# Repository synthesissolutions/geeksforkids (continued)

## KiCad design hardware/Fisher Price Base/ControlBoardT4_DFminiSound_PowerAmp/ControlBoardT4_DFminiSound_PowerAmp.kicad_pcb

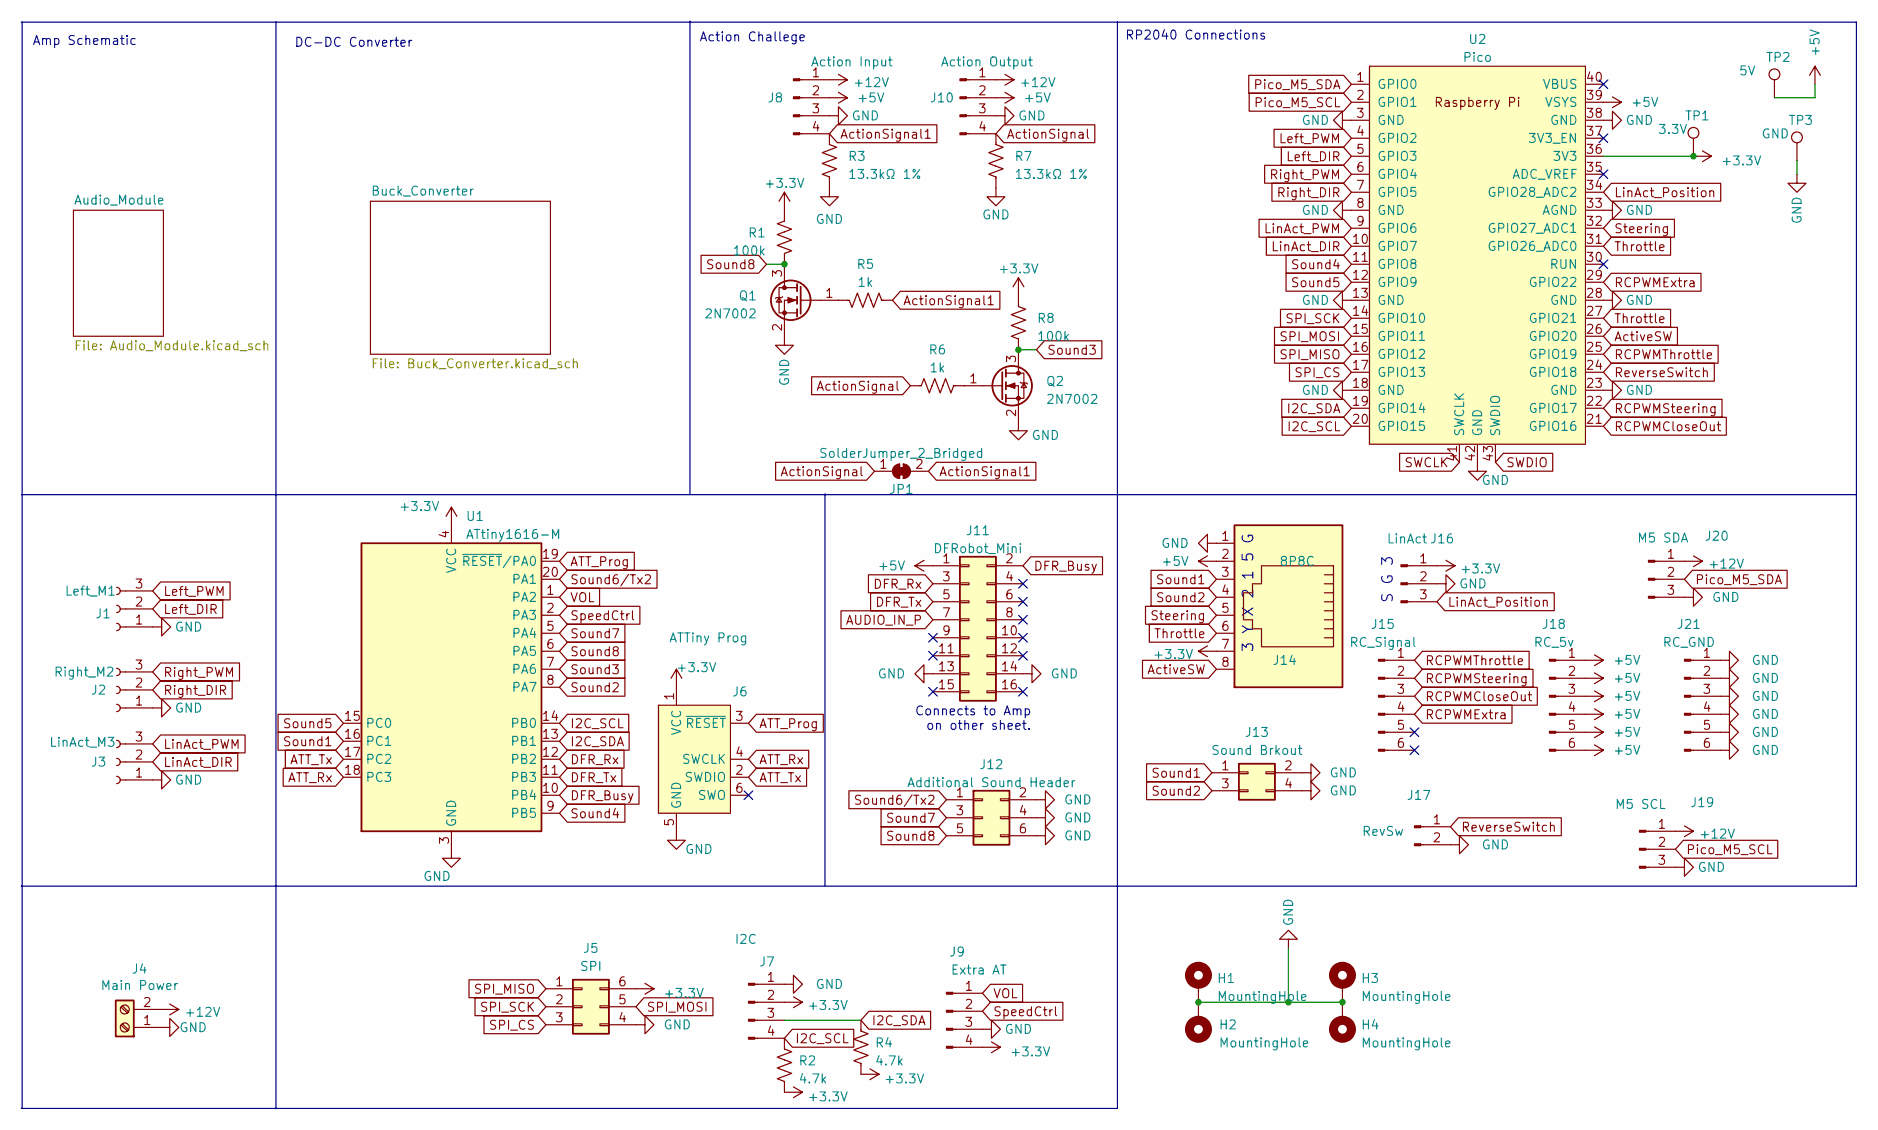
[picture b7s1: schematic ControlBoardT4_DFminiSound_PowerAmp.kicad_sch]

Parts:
H1, H2, H3, H4: MountingHole; MountingHole_2.7mm_M2.5_Pad
J1: Left_M1; PinHeader_1x03_P2.54mm_Vertical
J2: Right_M2; PinHeader_1x03_P2.54mm_Vertical
J3: LinAct_M3; PinHeader_1x03_P2.54mm_Vertical
J4: Main Power; TerminalBlock_bornier-2_P5.08mm
J5: SPI; PinHeader_2x03_P2.54mm_Vertical
J6: ATTiny Prog; Tag-Connect_TC2030-IDC-NL_2x03_P1.27mm_Vertical
J7: I2C; PinHeader_1x04_P2.54mm_Vertical
J8: Action Input; JST_XH_B4B-XH-A_1x04_P2.50mm_Vertical
J9: Extra AT; PinHeader_1x04_P2.54mm_Vertical
J10: Action Output; JST_XH_B4B-XH-A_1x04_P2.50mm_Vertical
J11: DFRobot_Mini; DFRobotMini_2x08_P2.54mm_Vertical
J12: Additional Sound Header; PinSocket_2x03_P2.54mm_Vertical
J13: Sound Brkout; PinSocket_2x02_P2.54mm_Vertical
J14: 8P8C; RJ45_x08_Tab_Up
J15: RC_Signal; PinSocket_1x06_P2.54mm_Vertical
J16: LinAct; JST_XH_B3B-XH-A_1x03_P2.54mm_Vertical
J17: RevSw; JST_XH_B2B-XH-A_1x02_P2.50mm_Vertical
J18: RC_5v; PinSocket_1x06_P2.54mm_Vertical
J19: M5 SCL; JST_XH_B3B-XH-A_1x03_P2.54mm_Vertical
J20: M5 SDA; JST_XH_B3B-XH-A_1x03_P2.54mm_Vertical
J21: RC_GND; PinSocket_1x06_P2.54mm_Vertical
JP1: SolderJumper_2_Bridged; SolderJumper-2_P1.3mm_Bridged_RoundedPad1.0x1.5mm
Q1, Q2: 2N7002; SOT-23; MPN C8545
R1, R8: 100k; R_0402_1005Metric; MPN C60491
R2, R4: 4.7k; R_0402_1005Metric; MPN C25900
R3, R7: 13.3kΩ 1%; R_0603_1608Metric; MPN C25952
R5, R6: 1k; R_0402_1005Metric; MPN C11702
TP1: 3.3V; TestPoint_Pad_1.5x1.5mm
TP2: 5V; TestPoint_Pad_1.5x1.5mm
TP3: GND; TestPoint_Pad_1.5x1.5mm
U1: ATtiny1616-M; VQFN-20-1EP_3x3mm_P0.4mm_EP1.7x1.7mm; MPN C507118
U2: Pico; RPi_Pico_SMD_TH

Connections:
+3.3V: J5.6, J6.1 (VCC), J7.2, J9.4, J14.7, J16.1, R1.1, R2.1, R4.1, R8.1, TP1.1, U1.4 (VCC), U2.36 (3V3)
+5V: J8.2, J10.2, J11.1, J14.2, J18.1, J18.2, J18.3, J18.4, J18.5, J18.6, TP2.1, U2.39 (VSYS); also elsewhere on the board
+12V: J4.2, J8.1, J10.1, J19.1, J20.1; also elsewhere on the board
ATT_Prog: J6.3 (~RESET), U1.19 (~RESET/PA0)
ATT_Rx: J6.4 (SWCLK), U1.18 (PC3)
ATT_Tx: J6.2 (SWDIO), U1.17 (PC2)
AUDIO_IN_P: J11.7; also elsewhere on the board
ActionSignal: J10.4, JP1.1 (A), R6.1, R7.1
ActionSignal1: J8.4, JP1.2 (B), R3.1, R5.1
ActiveSW: J14.8, U2.26 (GPIO20)
DFR_Busy: J11.2, U1.10 (PB4)
DFR_Rx: J11.3, U1.12 (PB2)
DFR_Tx: J11.5, U1.11 (PB3)
GND: H1.1, H2.1, H3.1, H4.1, J1.1, J2.1, J3.1, J4.1, J5.4, J6.5 (GND), J7.1, J8.3, J9.3, J10.3, J11.13, J11.14, J12.2, J12.4, J12.6, J13.2, J13.4, J14.1, J16.2, J17.2, J19.3, J20.3, J21.1, J21.2, J21.3, J21.4, J21.5, J21.6, Q1.2 (S), Q2.2 (S), R3.2, R7.2, TP3.1, U1.3 (GND), U1.21 (GND), U2.3 (GND), U2.8 (GND), U2.13 (GND), U2.18 (GND), U2.23 (GND), U2.28 (GND), U2.33 (AGND), U2.38 (GND), U2.42 (GND); also elsewhere on the board
I2C_SCL: J7.4, R2.2, U1.14 (PB0), U2.20 (GPIO15)
I2C_SDA: J7.3, R4.2, U1.13 (PB1), U2.19 (GPIO14)
Left_DIR: J1.2, U2.5 (GPIO3)
Left_PWM: J1.3, U2.4 (GPIO2)
LinAct_DIR: J3.2, U2.10 (GPIO7)
LinAct_PWM: J3.3, U2.9 (GPIO6)
LinAct_Position: J16.3, U2.34 (GPIO28_ADC2)
unnamed: Q1.1 (G), R5.2
unnamed: Q2.1 (G), R6.2
Pico_M5_SCL: J19.2, U2.2 (GPIO1)
Pico_M5_SDA: J20.2, U2.1 (GPIO0)
RCPWMCloseOut: J15.3, U2.21 (GPIO16)
RCPWMExtra: J15.4, U2.29 (GPIO22)
RCPWMSteering: J15.2, U2.22 (GPIO17)
RCPWMThrottle: J15.1, U2.25 (GPIO19)
ReverseSwitch: J17.1, U2.24 (GPIO18)
Right_DIR: J2.2, U2.7 (GPIO5)
Right_PWM: J2.3, U2.6 (GPIO4)
SPI_CS: J5.3, U2.17 (GPIO13)
SPI_MISO: J5.1, U2.16 (GPIO12)
SPI_MOSI: J5.5, U2.15 (GPIO11)
SPI_SCK: J5.2, U2.14 (GPIO10)
SWCLK: U2.41 (SWCLK)
SWDIO: U2.43 (SWDIO)
Sound1: J13.1, J14.3, U1.16 (PC1)
Sound2: J13.3, J14.4, U1.8 (PA7)
Sound3: Q2.3 (D), R8.2, U1.7 (PA6)
Sound4: U1.9 (PB5), U2.11 (GPIO8)
Sound5: U1.15 (PC0), U2.12 (GPIO9)
Sound6/Tx2: J12.1, U1.20 (PA1)
Sound7: J12.3, U1.5 (PA4)
Sound8: J12.5, Q1.3 (D), R1.2, U1.6 (PA5)
SpeedCtrl: J9.2, U1.2 (PA3)
Steering: J14.5, U2.32 (GPIO27_ADC1)
Throttle: J14.6, U2.27 (GPIO21), U2.31 (GPIO26_ADC0)
VOL: J9.1, U1.1 (PA2)

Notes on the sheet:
Connects to Amp on other sheet.
3 Y X 2 1 5 G
RP2040 Connections
Amp Schematic
DC-DC Converter
Action Challege
S G 3

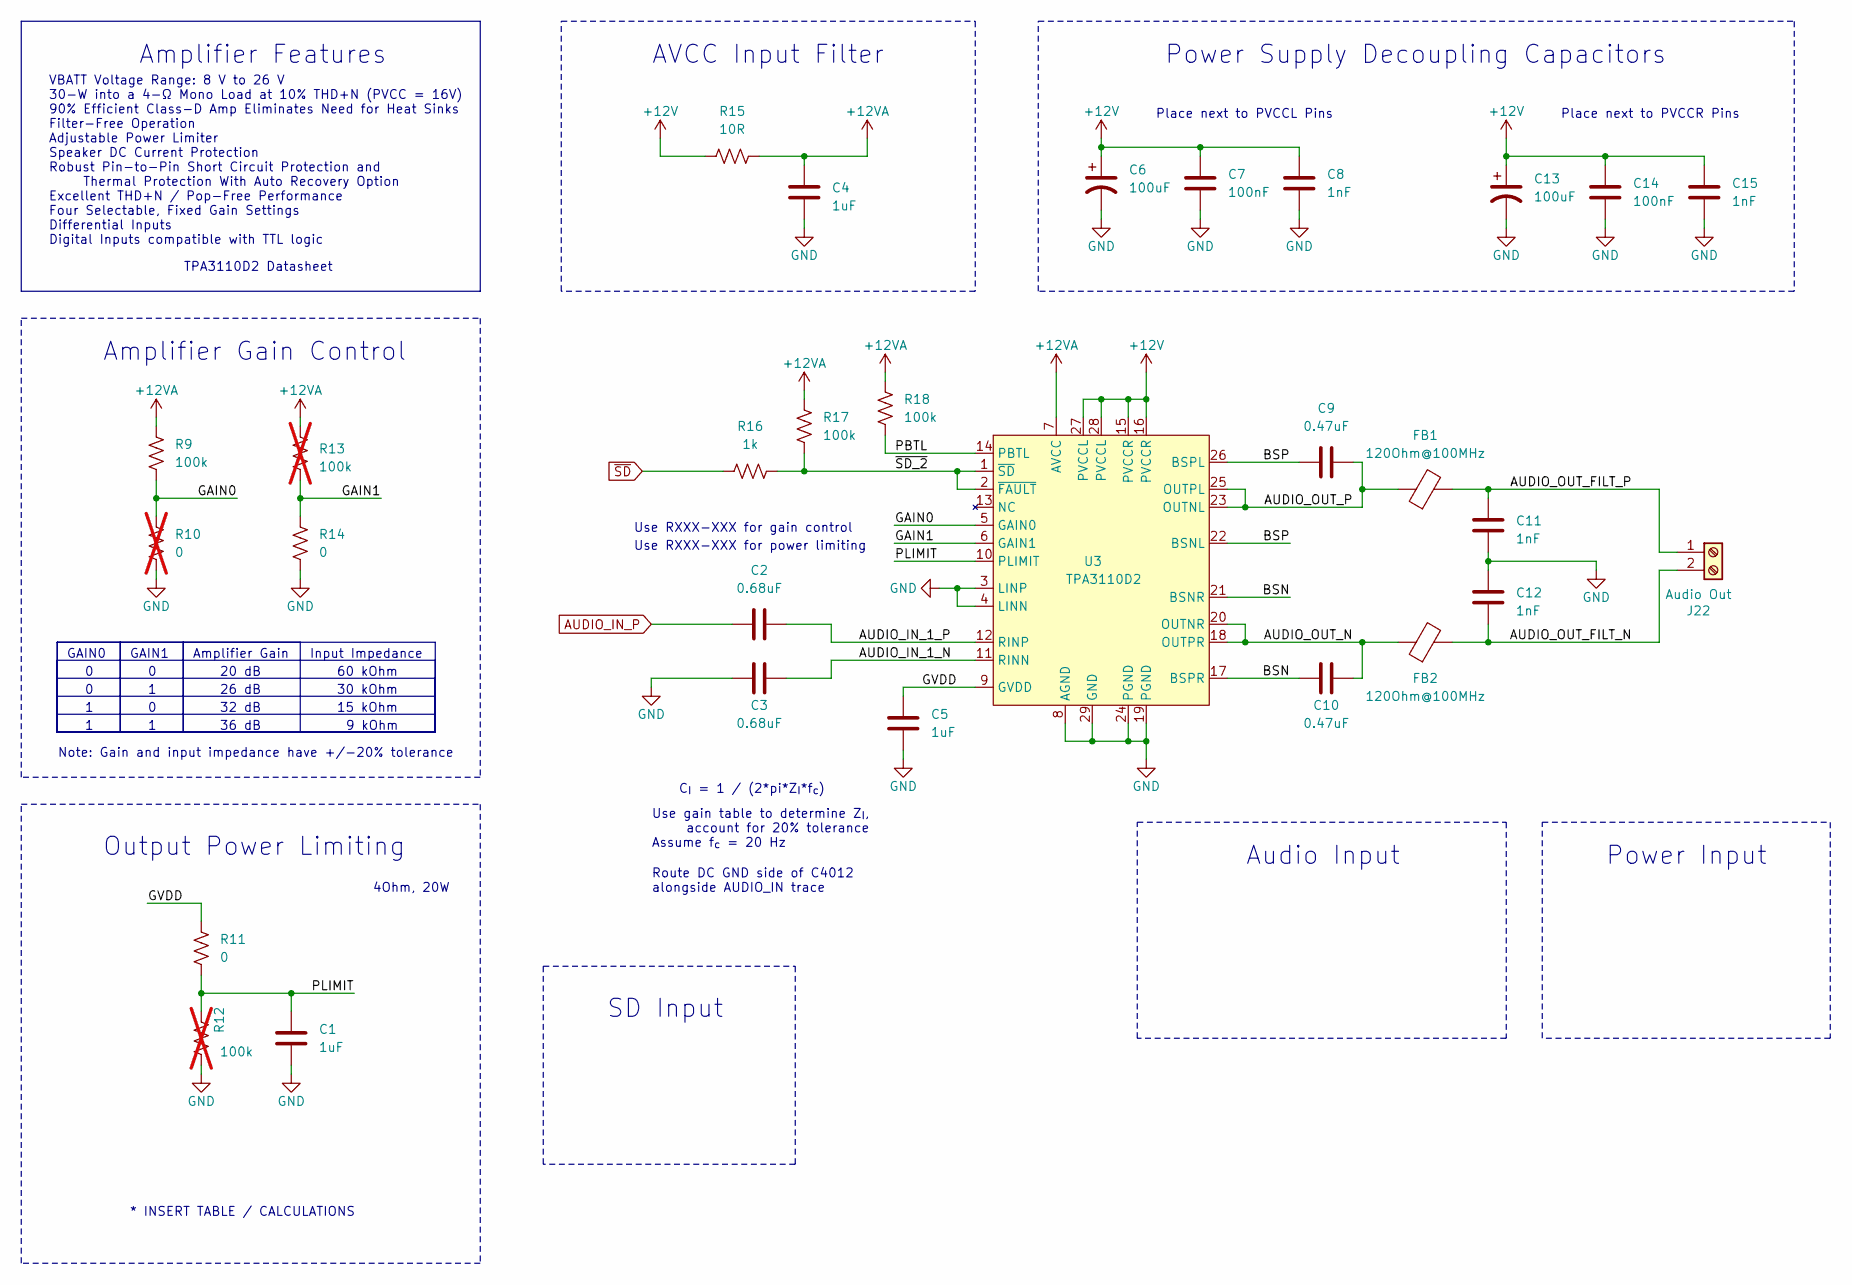
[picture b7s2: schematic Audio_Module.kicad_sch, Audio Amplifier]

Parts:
C1, C4, C5: 1uF; C_0402_1005Metric; MPN C1518208
C2, C3: 0.68uF; C_0402_1005Metric; MPN C113784
C6, C13: 100uF; CP_Radial_D8.0mm_P3.50mm; MPN C112510
C7, C14: 100nF; C_0402_1005Metric; MPN C105882
C8, C11, C12, C15: 1nF; C_0402_1005Metric; MPN C106205
C9, C10: 0.47uF; C_0402_1005Metric; MPN C437527
FB1, FB2: 120Ohm@100MHz; L_1206_3216Metric; MPN C3011219
J22: Audio Out; TerminalBlock_bornier-2_P5.08mm
R9, R17, R18: 100k; R_0402_1005Metric; MPN C60491
R10: 0; R_0402_1005Metric; MPN C17168; not fitted
R11, R14: 0; R_0402_1005Metric; MPN C17168
R12, R13: 100k; R_0402_1005Metric; MPN C60491; not fitted
R15: 10R; R_0603_1608Metric; MPN C22859
R16: 1k; R_0402_1005Metric; MPN C11702
U3: TPA3110D2; HTSSOP-28-1EP_4.4x9.7mm_P0.65mm_EP3.4x9.5mm_Mask2.4x6.17mm_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; MPN C30132

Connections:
+12V: C6.1, C7.1, C8.1, C13.1, C14.1, C15.1, R15.1, U3.15 (PVCCR), U3.16 (PVCCR), U3.27 (PVCCL), U3.28 (PVCCL); also elsewhere on the board
+12VA: C4.1, R9.1, R13.1, R15.2, R17.1, R18.1, U3.7 (AVCC)
/Audio_Module/AUDIO_IN_1_N: C3.1, U3.11 (RINN)
/Audio_Module/AUDIO_IN_1_P: C2.2, U3.12 (RINP)
/Audio_Module/AUDIO_OUT_FILT_N: C12.2, FB2.2, J22.2
/Audio_Module/AUDIO_OUT_FILT_P: C11.1, FB1.2, J22.1
/Audio_Module/AUDIO_OUT_N: C10.1, FB2.1, U3.18 (OUTPR), U3.20 (OUTNR)
/Audio_Module/AUDIO_OUT_P: C9.1, FB1.1, U3.23 (OUTNL), U3.25 (OUTPL)
/Audio_Module/BSN: C10.2, U3.17 (BSPR), U3.21 (BSNR)
/Audio_Module/BSP: C9.2, U3.22 (BSNL), U3.26 (BSPL)
/Audio_Module/GAIN0: R9.2, R10.1, U3.5 (GAIN0)
/Audio_Module/GAIN1: R13.2, R14.1, U3.6 (GAIN1)
/Audio_Module/GVDD: C5.1, R11.1, U3.9 (GVDD)
/Audio_Module/PBTL: R18.2, U3.14 (PBTL)
/Audio_Module/PLIMIT: C1.1, R11.2, R12.1, U3.10 (PLIMIT)
/Audio_Module/~SD_2: R16.2, R17.2, U3.1 (~SD), U3.2 (~FAULT)
AUDIO_IN_P: C2.1; also elsewhere on the board
GND: C1.2, C3.2, C4.2, C5.2, C6.2, C7.2, C8.2, C11.2, C12.1, C13.2, C14.2, C15.2, R10.2, R12.2, R14.2, U3.3 (LINP), U3.4 (LINN), U3.8 (AGND), U3.19 (PGND), U3.24 (PGND), U3.29 (GND); also elsewhere on the board
~SD: R16.1

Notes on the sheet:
30 kOhm
Route DC GND side of C4012 alongside AUDIO_IN trace
Use gain table to determine Z_{I}, account for 20% tolerance Assume f_{c} = 20 Hz
Use RXXX-XXX for power limiting
Amplifier Gain Control
GAIN0
Output Power Limiting
32 dB
C_{I} = 1 / (2*pi*Z_{I}*f_{c})
Use RXXX-XXX for gain control
20 dB
* INSERT TABLE / CALCULATIONS
SD Input
Audio Input
Note: Gain and input impedance have +/-20% tolerance
26 dB
VBATT Voltage Range: 8 V to 26 V 30-W into a 4-Ω Mono Load at 10% THD+N (PVCC = 16V) 90% Efficient Class-D Amp Eliminates Need for Heat Sinks Filter-Free Operation Adjustable Power Limiter Speaker DC Current Protection Robust Pin-to-Pin Short Circuit Protection and Thermal Protection With Auto Reco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
Amplifier Features
Amplifier Gain
Power Input
36 dB
4Ohm, 20W
TPA3110D2 Datasheet
AVCC Input Filter
15 kOhm
9 kOhm
Place next to PVCCR Pins
GAIN1
60 kOhm
Input Impedance
Power Supply Decoupling Capacitors
Place next to PVCCL Pins

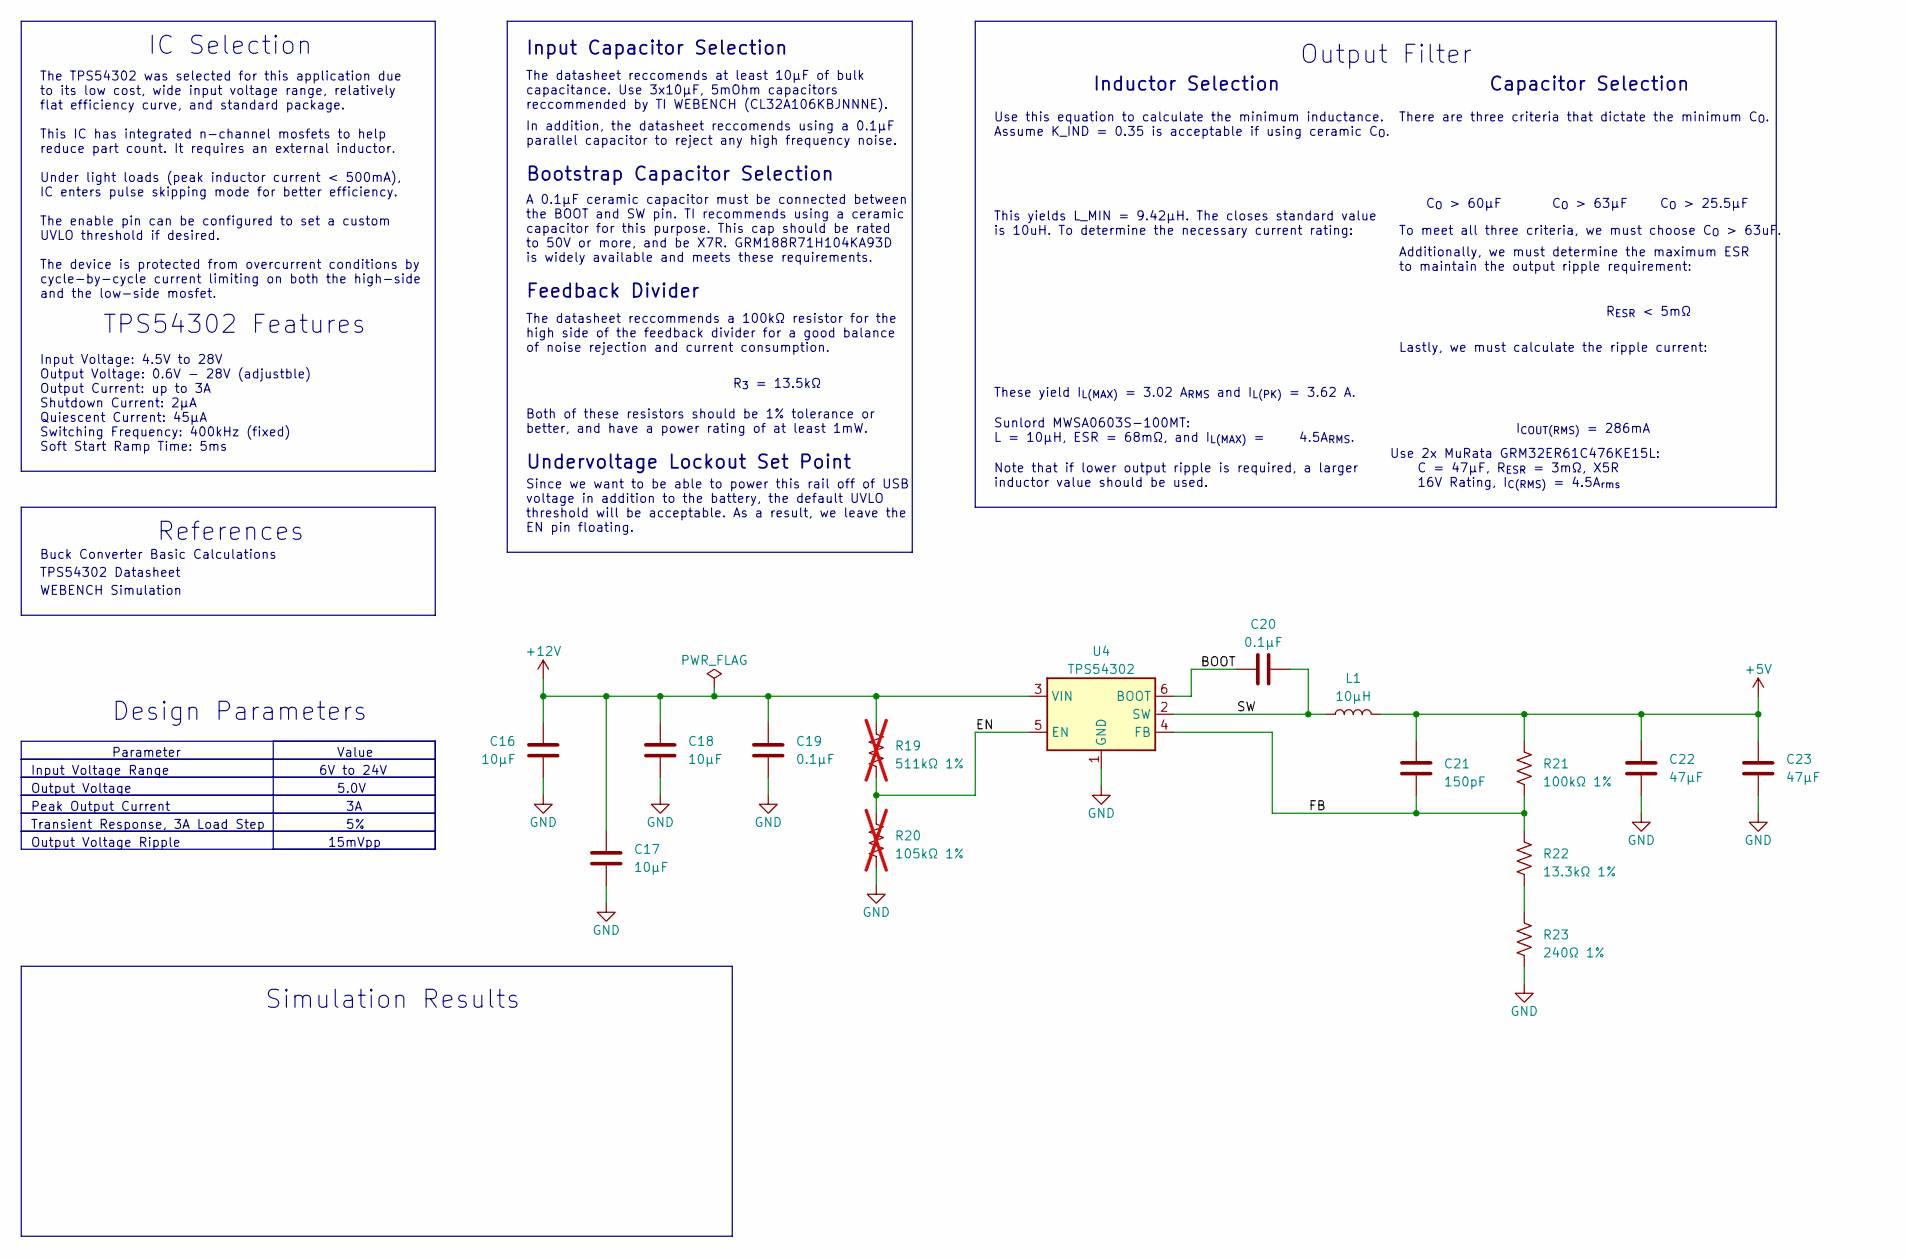
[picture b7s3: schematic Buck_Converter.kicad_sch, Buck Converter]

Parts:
C16, C17, C18: 10µF; C_1210_3225Metric; MPN C380537
C19, C20: 0.1µF; C_0603_1608Metric; MPN C77055
C21: 150pF; C_0603_1608Metric; MPN C527999
C22, C23: 47µF; C_1210_3225Metric; MPN C77101
L1: 10µH; L_Sunlord_MWSA0603S; MPN C132141
R19: 511kΩ 1%; R_0603_1608Metric; MPN C23194; not fitted
R20: 105kΩ 1%; R_0603_1608Metric; MPN C16840; not fitted
R21: 100kΩ 1%; R_0603_1608Metric; MPN C25803
R22: 13.3kΩ 1%; R_0603_1608Metric; MPN C25952
R23: 240Ω 1%; R_0603_1608Metric; MPN C23350
U4: TPS54302; SOT-23-6; MPN C311983

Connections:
+5V: C21.1, C22.1, C23.1, L1.2, R21.1; also elsewhere on the board
+12V: C16.1, C17.1, C18.1, C19.1, R19.1, U4.3 (VIN); also elsewhere on the board
/Buck_Converter/BOOT: C20.1, U4.6 (BOOT)
/Buck_Converter/EN: R19.2, R20.1, U4.5 (EN)
/Buck_Converter/FB: C21.2, R21.2, R22.1, U4.4 (FB)
/Buck_Converter/SW: C20.2, L1.1, U4.2 (SW)
GND: C16.2, C17.2, C18.2, C19.2, C22.2, C23.2, R20.2, R23.2, U4.1 (GND); also elsewhere on the board
unnamed: R22.2, R23.1

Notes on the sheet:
C_{O} > 60µF
Sunlord MWSA0603S-100MT: L = 10µH, ESR = 68mΩ, and I_{L(MAX)} = 4.5A_{RMS}.
R_{ESR} < 5mΩ
Inductor Selection
Output Voltage
These yield I_{L(MAX)} = 3.02 A_{RMS} and I_{L(PK)} = 3.62 A.
Output Voltage Ripple
In addition, the datasheet reccomends using a 0.1µF parallel capacitor to reject any high frequency noise.
Note that if lower output ripple is required, a larger inductor value should be used.
The TPS54302 was selected for this application due to its low cost, wide input voltage range, relatively flat efficiency curve, and standard package. This IC has integrated n-channel mosfets to help reduce part count. It requires an external inductor. Under light loads (peak inductor current < 500m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
IC Selection
Undervoltage Lockout Set Point
Input Voltage Range
This yields L_MIN = 9.42µH. The closes standard value is 10uH. To determine the necessary current rating:
TPS54302 Features
Since we want to be able to power this rail off of USB voltage in addition to the battery, the default UVLO threshold will be acceptable. As a result, we leave the EN pin floating.
15mVpp
The datasheet reccommends a 100kΩ resistor for the high side of the feedback divider for a good balance of noise rejection and current consumption.
Use 2x MuRata GRM32ER61C476KE15L: C = 47µF, R_{ESR} = 3mΩ, X5R 16V Rating, I_{C(RMS)} = 4.5A_{rms}
Capacitor Selection
The datasheet reccomends at least 10µF of bulk capacitance. Use 3x10µF, 5mOhm capacitors reccommended by TI WEBENCH (CL32A106KBJNNNE).
Feedback Divider
Simulation Results
References
Output Filter
WEBENCH Simulation
Buck Converter Basic Calculations
6V to 24V
Use this equation to calculate the minimum inductance. Assume K_IND = 0.35 is acceptable if using ceramic C_{O}.
Input Capacitor Selection
Design Parameters
There are three criteria that dictate the minimum C_{O}.
Parameter
5.0V
R_{3} = 13.5kΩ
C_{O} > 25.5µF
To meet all three criteria, we must choose C_{O} > 63uF.
Additionally, we must determine the maximum ESR to maintain the output ripple requirement:
I_{COUT(RMS)} = 286mA
Bootstrap Capacitor Selection

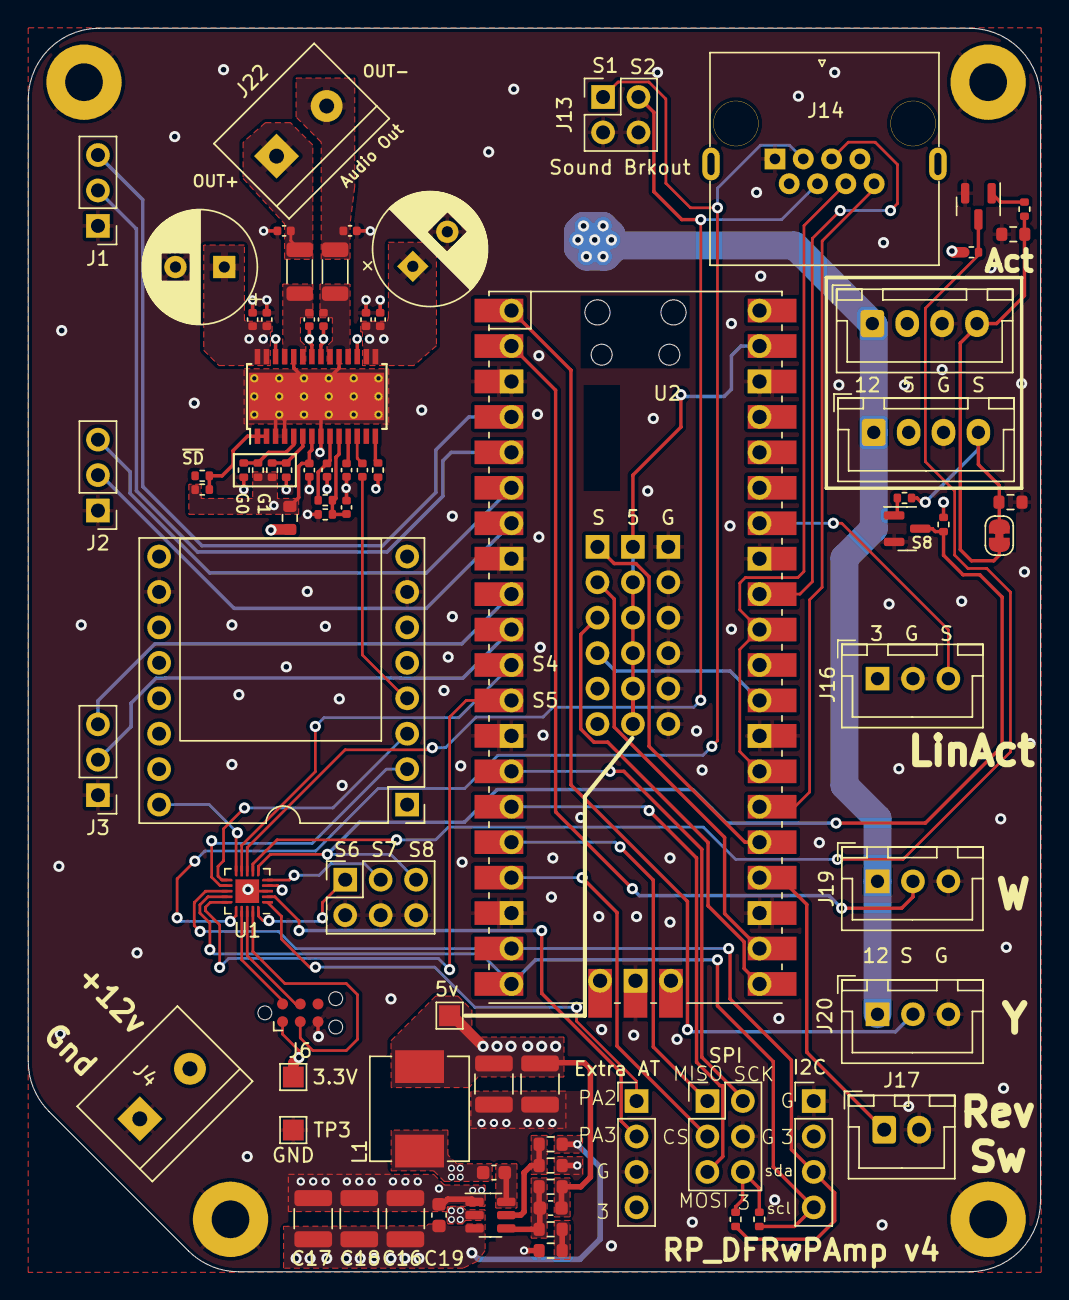
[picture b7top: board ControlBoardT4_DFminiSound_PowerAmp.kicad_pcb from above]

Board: 4 copper layers, 72.6 x 89.1 mm, 85 parts (0 on the bottom side), 68 nets.

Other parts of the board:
5v: 5V; TestPoint_Pad_1.5x1.5mm

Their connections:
+5V: 5v.1; also elsewhere on the board

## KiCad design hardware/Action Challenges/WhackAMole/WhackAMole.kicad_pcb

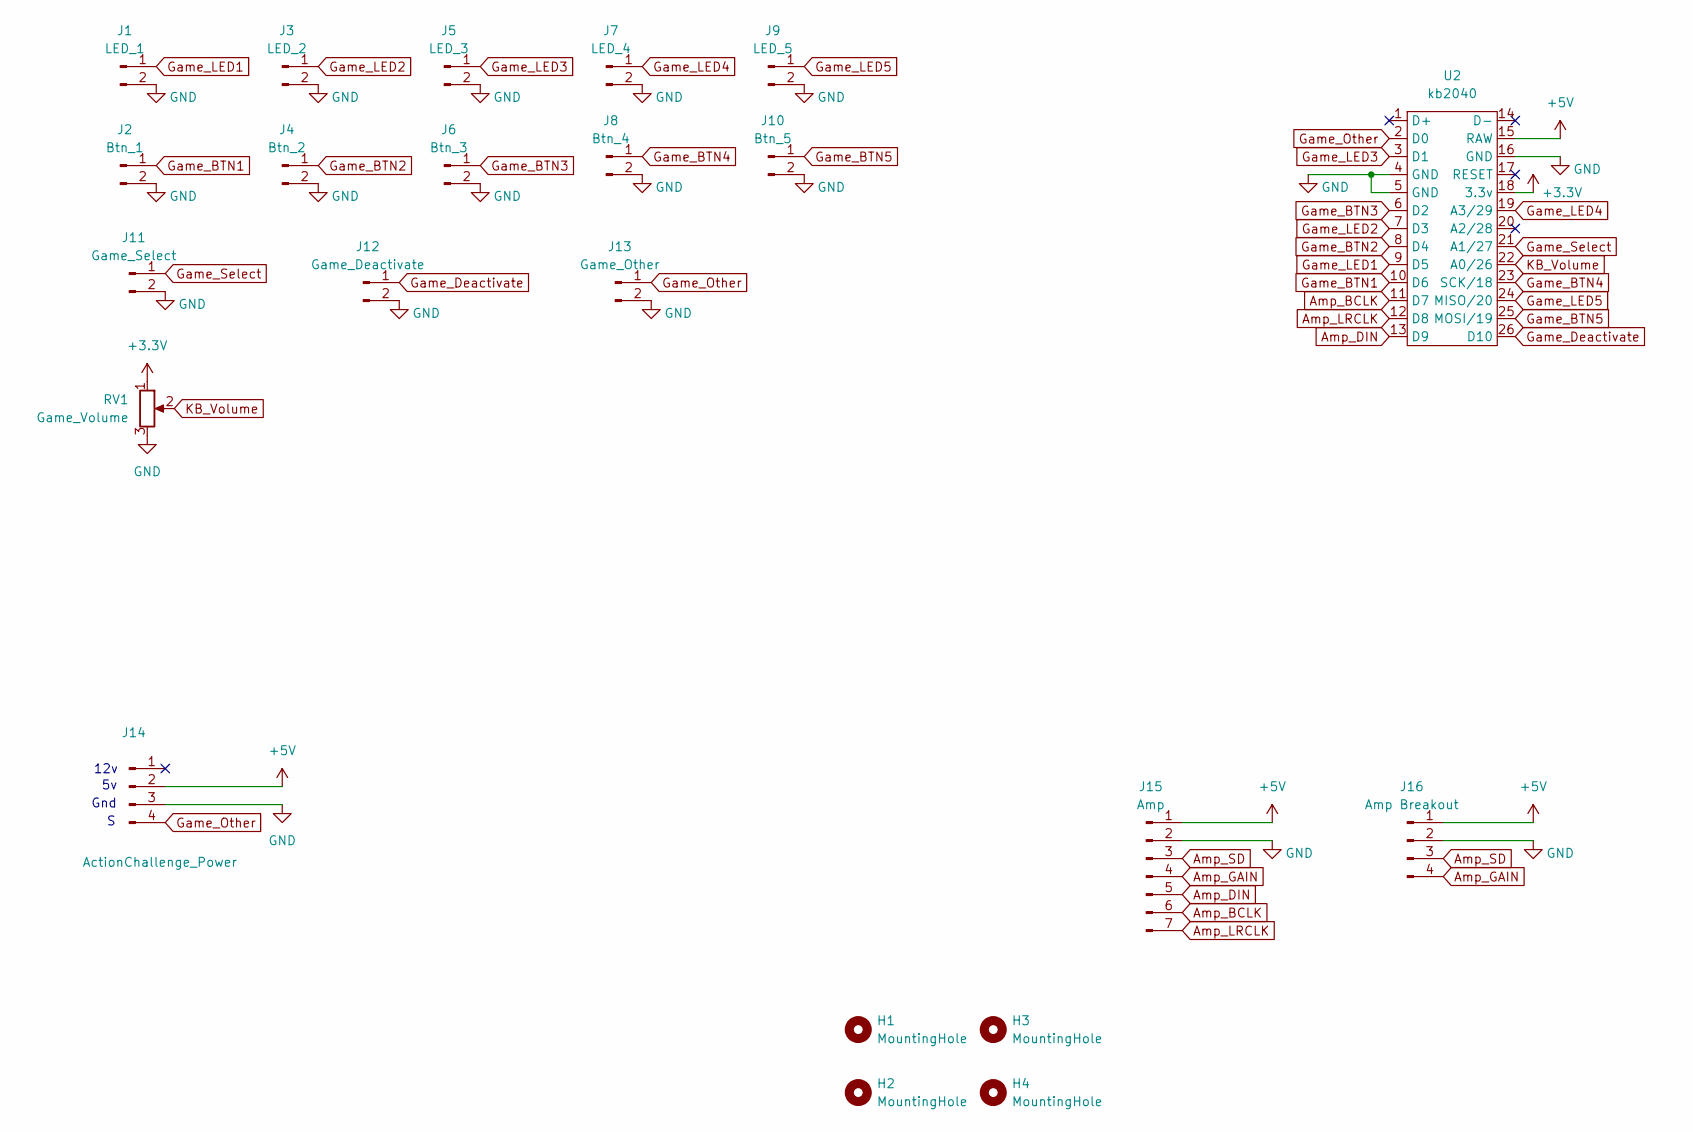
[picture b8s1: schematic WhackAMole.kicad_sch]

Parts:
H1, H2, H3, H4: MountingHole; MountingHole_2.7mm_M2.5
J1: LED_1; JST_XH_B2B-XH-A_1x02_P2.50mm_Vertical
J2: Btn_1; JST_XH_B2B-XH-A_1x02_P2.50mm_Vertical
J3: LED_2; JST_XH_B2B-XH-A_1x02_P2.50mm_Vertical
J4: Btn_2; JST_XH_B2B-XH-A_1x02_P2.50mm_Vertical
J5: LED_3; JST_XH_B2B-XH-A_1x02_P2.50mm_Vertical
J6: Btn_3; JST_XH_B2B-XH-A_1x02_P2.50mm_Vertical
J7: LED_4; JST_XH_B2B-XH-A_1x02_P2.50mm_Vertical
J8: Btn_4; JST_XH_B2B-XH-A_1x02_P2.50mm_Vertical
J9: LED_5; JST_XH_B2B-XH-A_1x02_P2.50mm_Vertical
J10: Btn_5; JST_XH_B2B-XH-A_1x02_P2.50mm_Vertical
J11: Game_Select; JST_XH_B2B-XH-A_1x02_P2.50mm_Vertical
J12: Game_Deactivate; JST_XH_B2B-XH-A_1x02_P2.50mm_Vertical
J13: Game_Other; PinSocket_1x02_P2.54mm_Vertical
J14: ActionChallenge_Power; JST_XH_B4B-XH-A_1x04_P2.50mm_Vertical
J15: Amp; Adafruit_Max98357A_Breakout
J16: Amp Breakout; PinHeader_1x04_P2.54mm_Vertical
RV1: Game_Volume; JST_XH_B3B-XH-A_1x03_P2.50mm_Vertical
U2: kb2040

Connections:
+3.3V: RV1.1, U2.18 (3.3v)
+5V: J14.2, J15.1, J16.1, U2.15 (RAW)
Amp_BCLK: J15.6, U2.11 (D7)
Amp_DIN: J15.5, U2.13 (D9)
Amp_GAIN: J15.4, J16.4
Amp_LRCLK: J15.7, U2.12 (D8)
Amp_SD: J15.3, J16.3
GND: J1.2, J2.2, J3.2, J4.2, J5.2, J6.2, J7.2, J8.2, J9.2, J10.2, J11.2, J12.2, J13.2, J14.3, J15.2, J16.2, RV1.3, U2.4 (GND), U2.5 (GND), U2.16 (GND)
Game_BTN1: J2.1, U2.10 (D6)
Game_BTN2: J4.1, U2.8 (D4)
Game_BTN3: J6.1, U2.6 (D2)
Game_BTN4: J8.1, U2.23 (SCK/18)
Game_BTN5: J10.1, U2.25 (MOSI/19)
Game_Deactivate: J12.1, U2.26 (D10)
Game_LED1: J1.1, U2.9 (D5)
Game_LED2: J3.1, U2.7 (D3)
Game_LED3: J5.1, U2.3 (D1)
Game_LED4: J7.1, U2.19 (A3/29)
Game_LED5: J9.1, U2.24 (MISO/20)
Game_Other: J13.1, J14.4, U2.2 (D0)
Game_Select: J11.1, U2.21 (A1/27)
KB_Volume: RV1.2, U2.22 (A0/26)

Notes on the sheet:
Gnd
12v

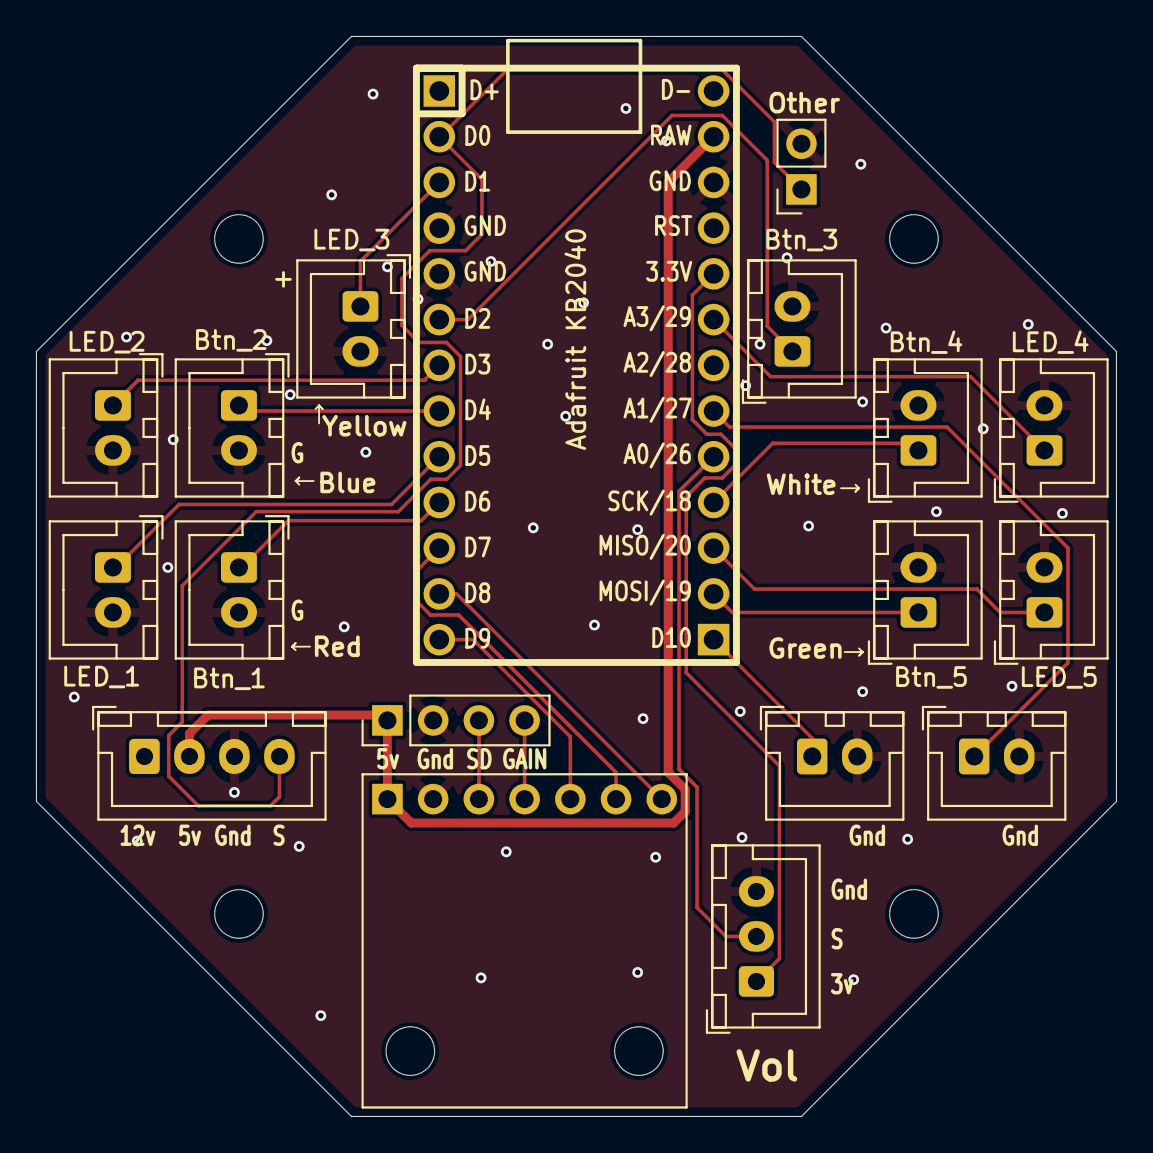
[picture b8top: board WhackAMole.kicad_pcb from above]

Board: 2 copper layers, 60.0 x 60.0 mm, 22 parts (0 on the bottom side), 22 nets.

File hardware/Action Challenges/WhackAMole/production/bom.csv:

Designator,Footprint,Quantity,Value,LCSC Part #
J1,JST_XH_B2B-XH-A_1x02_P2.50mm_Vertical,1,LED_1,
J10,JST_XH_B2B-XH-A_1x02_P2.50mm_Vertical,1,Btn_5,
J11,JST_XH_B2B-XH-A_1x02_P2.50mm_Vertical,1,Game_Select,
J12,JST_XH_B2B-XH-A_1x02_P2.50mm_Vertical,1,Game_Deactivate,
J13,PinSocket_1x02_P2.54mm_Vertical,1,Game_Other,
J14,JST_XH_B4B-XH-A_1x04_P2.50mm_Vertical,1,ActionChallenge_Power,
J15,Adafruit_Max98357A_Breakout,1,Amp,
J16,PinHeader_1x04_P2.54mm_Vertical,1,Amp Breakout,
J2,JST_XH_B2B-XH-A_1x02_P2.50mm_Vertical,1,Btn_1,
J3,JST_XH_B2B-XH-A_1x02_P2.50mm_Vertical,1,LED_2,
J4,JST_XH_B2B-XH-A_1x02_P2.50mm_Vertical,1,Btn_2,
J5,JST_XH_B2B-XH-A_1x02_P2.50mm_Vertical,1,LED_3,
J6,JST_XH_B2B-XH-A_1x02_P2.50mm_Vertical,1,Btn_3,
J7,JST_XH_B2B-XH-A_1x02_P2.50mm_Vertical,1,LED_4,
J8,JST_XH_B2B-XH-A_1x02_P2.50mm_Vertical,1,Btn_4,
J9,JST_XH_B2B-XH-A_1x02_P2.50mm_Vertical,1,LED_5,
RV1,JST_XH_B3B-XH-A_1x03_P2.50mm_Vertical,1,Game_Volume,
U2,kb2040,1,kb2040,

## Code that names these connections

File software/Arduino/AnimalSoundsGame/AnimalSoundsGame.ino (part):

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#define BUTTON_COUNT  5
#define SOUND_FOLDER_COUNT  5

#define BUSY_PIN      5  //PB4
#define VOLUME_PIN    8  //PB1

#define BUTTON_1_PIN     0     // PA4  - Red
#define BUTTON_2_PIN     16    // PA3  - Blue
#define BUTTON_3_PIN     3     // PA7  - Yellow
#define BUTTON_4_PIN     2     // PA6  - White
#define BUTTON_5_PIN     1     // PA5  - Green

#define LED_1_PIN     15    // PA2  - Red
#define LED_2_PIN     14    // PA1  - Blue
#define LED_3_PIN     4     // PB5  - Yellow
#define LED_4_PIN     13    // PC3  - White
#define LED_5_PIN     12    // PC2  - Green

#define RANDOM_SEED_PIN   16  // PC2 - Unconnected

#define ANIMAL_SOUNDS_FOLDER    1
#define ANIMAL_NAMES_FOLDER     2
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
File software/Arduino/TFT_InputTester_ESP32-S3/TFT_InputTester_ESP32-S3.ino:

#include <SPI.h>
#include <Wire.h>
#include <Adafruit_GFX.h>
#include <Adafruit_ST7789.h>

#define TFT_CS        7
#define TFT_RST       40 // Or set to -1 and connect to Arduino RESET pin
#define TFT_DC        39
#define TFT_BACKLIGHT 45

#define BUTTON_A  5
#define BUTTON_B  6

#define PIN_JOYSTICK_STEERING A3
#define PIN_JOYSTICK_THROTTLE A1
#define PIN_RC_STEERING       12
#define PIN_RC_THROTTLE       13
#define PIN_SOUND_1           A4
#define PIN_SOUND_2           A0
#define PIN_ACTIVE_SWITCH     A2

Adafruit_ST7789 display = Adafruit_ST7789(TFT_CS, TFT_DC, TFT_RST);

int throttle = 0;
int steering = 0;

int rcThrottle = 0;
int rcSteering = 0;

bool isAnalog = true;
bool showRc = false;

int joystickSteeringPwm = 0;
bool joystickSteeringSignalHigh = false;
int joystickSteeringPulseStart = 0;

int joystickThrottlePwm = 0;
bool joystickThrottleSignalHigh = false;
int joystickThrottlePulseStart = 0;

int rcSteeringPwm = 0;
bool rcSteeringSignalHigh = false;
int rcSteeringPulseStart = 0;

int rcThrottlePwm = 0;
bool rcThrottleSignalHigh = false;
int rcThrottlePulseStart = 0;

void setup() {
  Serial.begin(115200);

  // Pin 45 is the backlight pin, set to 1 to get full brightness - uses PWM signal for other brightness levels?
  pinMode(TFT_BACKLIGHT, OUTPUT);
  digitalWrite(TFT_BACKLIGHT, 1);

  display.init(135, 240);
  display.setRotation(1);
  
  display.fillScreen(ST77XX_BLACK);
  delay(1000);

  display.setRotation(1);

  pinMode(BUTTON_A, INPUT_PULLUP);
  pinMode(BUTTON_B, INPUT_PULLUP);

  pinMode(PIN_SOUND_1, INPUT_PULLUP);
  pinMode(PIN_SOUND_2, INPUT_PULLUP);

  pinMode(PIN_ACTIVE_SWITCH, INPUT_PULLDOWN);

  display.setTextSize(2);
  display.setTextColor(ST77XX_WHITE);
  display.setCursor(0, 0);
  display.print("A - Analog (default)");
  display.setCursor(0, 30);
  display.print("B - PWM");
  display.setCursor(0, 60);
  display.print("C - Show RC");

  delay(3000);

  display.fillScreen(ST77XX_BLACK);

  // text display tests
  display.setTextSize(2);
  display.setTextColor(ST77XX_WHITE);
  display.setCursor(0, 0);
  display.print("Throttle");
  display.setCursor(0, 28);
  display.print("Steering");

  display.setCursor(0, 56);
  display.print("Sound 1");
  display.setCursor(0, 84);
  display.print("Sound 2");

  display.setCursor(0, 112);
  display.print("Active");

  display.setCursor(180, 0);
  display.print("RC");
  display.setCursor(180, 28);
  display.print("RC");

  attachInterrupt(digitalPinToInterrupt(PIN_JOYSTICK_STEERING), &joystickSteeringIRQHandler, CHANGE);
  attachInterrupt(digitalPinToInterrupt(PIN_JOYSTICK_THROTTLE), &joystickThrottleIRQHandler, CHANGE);
  attachInterrupt(digitalPinToInterrupt(PIN_RC_STEERING), &rcSteeringIRQHandler, CHANGE);
  attachInterrupt(digitalPinToInterrupt(PIN_RC_THROTTLE), &rcThrottleIRQHandler, CHANGE);   
}

void loop() {
  if(!digitalRead(BUTTON_A)) {
    Serial.println("Button A Pressed");
    isAnalog = true;
  }
  if(!digitalRead(BUTTON_B)) {
    Serial.println("Button B Pressed");
    isAnalog = false;
  }

  display.fillRect(106, 0, 106, 130, ST77XX_BLACK);

  if (isAnalog) {
    throttle = analogRead(PIN_JOYSTICK_THROTTLE);
    steering = analogRead(PIN_JOYSTICK_STEERING);

    throttle = map(throttle, 0, 4095, 0, 1023);
    steering = map(steering, 0, 4095, 0, 1023);
  } else {
    throttle = joystickThrottlePwm;
    steering = joystickSteeringPwm;    
  }

  display.setCursor(106, 0);
  display.print(throttle);

  display.setCursor(106, 28);
  display.print(steering);

  if (showRc) {
    display.setCursor(83, 0);
    display.print(rcThrottlePwm);
  
    display.setCursor(83, 28);
    display.print(rcSteeringPwm);  
  }

  if (!digitalRead(PIN_SOUND_1)) {
    display.setCursor(106, 56);
    display.print("On");
  } else {
    display.setCursor(106, 56);
    display.print("Off");
  } 

  if (!digitalRead(PIN_SOUND_2)) {
    display.setCursor(106, 84);
    display.print("On");
  } else {
    display.setCursor(106, 84);
    display.print("Off");
  }

  if (digitalRead(PIN_ACTIVE_SWITCH)) {
    display.setCursor(106, 112);
    display.print("On");
  } else {
    display.setCursor(106, 112);
    display.print("Off");
  }

  delay(100);
}

void joystickSteeringIRQHandler() {
  if(digitalRead(PIN_JOYSTICK_STEERING) == 1){
    if (!joystickSteeringSignalHigh) {
      // rising edge of the PWM signal
      // record when the pulse started
      joystickSteeringPulseStart = micros();
      joystickSteeringSignalHigh = true;
    }
  } else if (joystickSteeringSignalHigh) {
    // falling edge of the PWM signal
    // record the duty cycle in microseconds
    joystickSteeringPwm = micros() - joystickSteeringPulseStart;

    // reset for the next pulse
    joystickSteeringSignalHigh = false;
  }
}

void joystickThrottleIRQHandler() {
  if(digitalRead(PIN_JOYSTICK_THROTTLE) == 1){
    if (!joystickThrottleSignalHigh) {
      // rising edge of the PWM signal
      // record when the pulse started
      joystickThrottlePulseStart = micros();
      joystickThrottleSignalHigh = true;
    }
  } else if (joystickThrottleSignalHigh) {
    // falling edge of the PWM signal
    // record the duty cycle in microseconds
    joystickThrottlePwm = micros() - joystickThrottlePulseStart;

    // reset for the next pulse
    joystickThrottleSignalHigh = false;
  }
}

void rcSteeringIRQHandler() {
  if(digitalRead(PIN_RC_STEERING) == 1){
    if (!rcSteeringSignalHigh) {
      showRc = true;
      // rising edge of the PWM signal
      // record when the pulse started
      rcSteeringPulseStart = micros();
      rcSteeringSignalHigh = true;
    }
  } else if (rcSteeringSignalHigh) {
    // falling edge of the PWM signal
    // record the duty cycle in microseconds
    rcSteeringPwm = micros() - rcSteeringPulseStart;

    // reset for the next pulse
    rcSteeringSignalHigh = false;
  }
}

void rcThrottleIRQHandler() {
  if(digitalRead(PIN_RC_THROTTLE) == 1){
    if (!rcThrottleSignalHigh) {
      // rising edge of the PWM signal
      // record when the pulse started
      rcThrottlePulseStart = micros();
      rcThrottleSignalHigh = true;
    }
  } else if (rcThrottleSignalHigh) {
    // falling edge of the PWM signal
    // record the duty cycle in microseconds
    rcThrottlePwm = micros() - rcThrottlePulseStart;

    // reset for the next pulse
    rcThrottleSignalHigh = false;
  }
}
